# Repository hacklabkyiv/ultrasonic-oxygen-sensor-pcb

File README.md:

# ultrasonic-oxygen-sensor-pcb
OSHW Ultrasonic Oxygen Concentration Sensor

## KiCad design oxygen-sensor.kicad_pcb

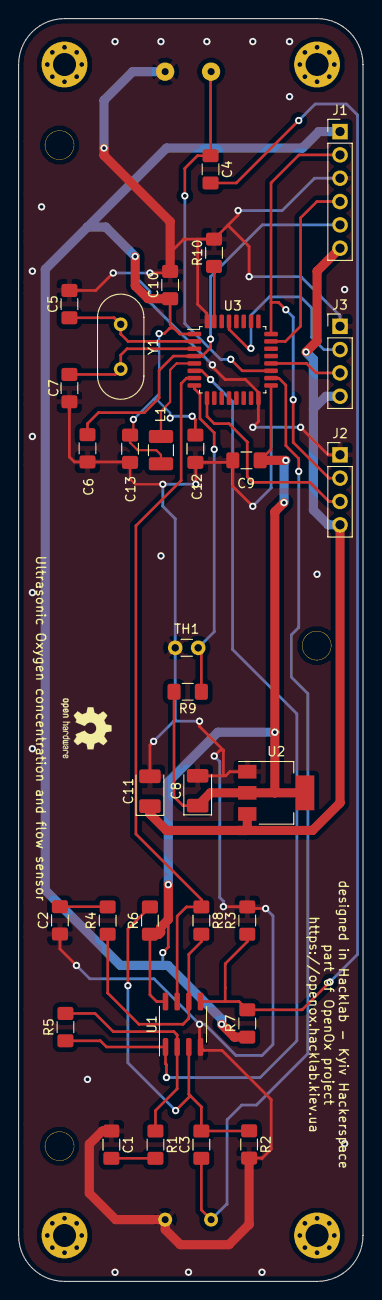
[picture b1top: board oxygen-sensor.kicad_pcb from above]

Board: 2 copper layers, 37.5 x 137.5 mm, 37 parts (1 on the bottom side), 24 nets.

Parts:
 : MountingHole_2.5mm_Pad_Via
  : MountingHole_2.5mm_Pad_Via
 #2,  #3: MountingHole_2.5mm_Pad_Via
C1, C2, C3, C4: 10nF; C_1206_3216Metric_Pad1.42x1.75mm_HandSolder
C5, C7: C_Small; C_1206_3216Metric_Pad1.42x1.75mm_HandSolder
C6, C9, C10: 100n; C_1206_3216Metric_Pad1.42x1.75mm_HandSolder
C8, C11: 100uF; CP_EIA-3528-21_Kemet-B_Pad1.50x2.35mm_HandSolder
C12: 10n; C_1206_3216Metric_Pad1.42x1.75mm_HandSolder
C13: 1uF; C_1206_3216Metric_Pad1.42x1.75mm_HandSolder
J1: DEBUG; PinHeader_1x06_P2.54mm_Vertical
J2: UART; PinHeader_1x04_P2.54mm_Vertical
J3: I2C; PinHeader_1x04_P2.54mm_Vertical
L1: 22uH; L_1210_3225Metric_Pad1.42x2.65mm_HandSolder
MK1: Sensor; Flow-sensor
R1, R4: 1k; R_1206_3216Metric_Pad1.42x1.75mm_HandSolder
R2, R3, R6, R7: 1M; R_1206_3216Metric_Pad1.42x1.75mm_HandSolder
R5, R8: 100k; R_1206_3216Metric_Pad1.42x1.75mm_HandSolder
R9: 10k; R_1206_3216Metric_Pad1.42x1.75mm_HandSolder
R10: R_Small; R_1206_3216Metric_Pad1.42x1.75mm_HandSolder
TH1: 10k; C_Disc_D3.0mm_W1.6mm_P2.50mm
U1: LM358; SOIC-8_3.9x4.9mm_P1.27mm
U2: LD1117S33TR_SOT223; SOT-223-3_TabPin2
U3: STM32F030K6Tx; LQFP-32_7x7mm_P0.8mm
Y1: Crystal; Crystal_HC49-4H_Vertical

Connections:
+3V3: C8.1, C9.1, C10.1, C12.2, C13.2, J1.1, L1.2, R6.1, R7.1, R9.2, U1.8, U2.2, U3.1, U3.17
+5V: C11.1, J1.6, J2.4, J3.4, U2.3
/NRST: C6.2, J1.5, U3.4
/NTC: R9.1, TH1.2, U3.8
/OUT1: R5.1, U1.1, U3.6
/OUT2: R8.1, U1.7, U3.7
/PWM1: C3.1, MK1.2, U3.18
/PWM2: C4.1, MK1.4, U3.19
/SWCLK: J1.2, J2.2, U3.24
/SWDIO: J1.4, U3.23
GND: C1.1, C2.1, C5.2, C6.1, C7.2, C8.2, C9.2, C10.2, C11.2, C12.1, C13.1, J1.3, J2.1, J3.1, MK1.1, MK1.3, R2.2, R3.2, R10.2, TH1.1, U1.4, U2.1, U3.16, U3.32
unnamed: C1.2, R1.2
unnamed: C2.2, R4.2
unnamed: C3.2, R2.1, R6.2, U1.3
unnamed: C4.2, R3.1, R7.2, U1.5
unnamed: C5.1, U3.2, Y1.1
unnamed: C7.1, U3.3, Y1.2
unnamed: J2.3, U3.9
unnamed: J3.2, U3.29
unnamed: J3.3, U3.20
unnamed: L1.1, U3.5
unnamed: R1.1, R5.2, U1.2
unnamed: R4.1, R8.2, U1.6
unnamed: R10.1, U3.31

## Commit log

2020-05-12 First version added
2020-05-14 Fix short-circuit error
